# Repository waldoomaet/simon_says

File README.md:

# Inspiration
[Simon Game from Wokwi](https://wokwi.com/projects/344891334169985618)

Pretty much the same game. My version includes the board design and the game logic made with OOP (as a way to dive with this paradigm into embedded systems). Go check it out to see the simulation!

# Description
This is a personal project called Simon Says (or "Simon Dice", in Spanish).

Pretty much is an Arduino Nano with four buttons, four LEDs and a buzzer (and some displays for score), which randomly generates a pattern that the user must match. Match it, and you get a point, fail, and it is game over. Pretty simple! There is also an easier game mode, intended for smaller kids, that just generates a one-step pattern (so the game simplifies to matching the color).

# Hardware
Parts list:
* 1x Arduino Nano
* 1x SPDT switch 
* 1x Terminal block
* 1x 5v buzzer
* 2x CD4033 Decade Counter IC
* 2x common cathode 7-segment display
* 4x push buttons (preferably with color caps)
* 4x LEDs (preferably that match the caps' colors)
* 6x 1k resistors

The circuit board was made using KiCad, and there are two versions:
* A single copper side version (not tested)
* A double copper side version

Each version includes all the necessary files to fabricate the board with services such as JLCPCB.

It should be possible to also use some of the homemade methods (such as the iron method), but I never tried it.

# Hardware limitations

1. THE BOARD NEED TWO JUMPERS. I didn't notice that I used two pins of the Arduino that can't be used as digital I/O (A6 and A7), so two jumpers from A7 to A5 and from A6 to A4 are necessary.

2. Due to me using some old and obscure CD4033 Decade Counter ICs as a way to get rid of them, you can only:
    * Show numbers on the displays (and none of the hex letters that you normally could use)
    * Reset the count back to 0 or increment it. This is particularly awful since you can't set a specific number or decrement the count without first resetting the count and then increment all the way to the number that you want 

3. Due to me being too cheap to use an individual pin, of the many that the Arduino offers, for every led/button, I ended up sharing the same pin for a button and a LED, and then switch between the pin being an output or an input as needed. This ended up biting me right in the butt, as this was:

    * More annoying than it needed to be, implementing in software
    * Limiting in the sense that you can't easily, for example, play an animation and also get user input

# Software

On the software side of things, there are two important directories:
* *./src*, which have the initializing/main code
* *./lib/game_system*, which have all the game logic

The files on those directories are the main one to change in order to make any modification to the game. 

For example, to change from the normal game mode to the simpler one, you have to go tho the *main.cpp* in *./src*, and change the method called in loop:

```cpp
void loop()
{
    // This is the normal game mode. Default
    gameSystem.gameMode1();

    // Simpler version (matching colors)
    // gameSystem.gameMode2();
    
    // This is some kind of "menu" to ask every time the desired game mode
    // gameSystem.selectGameMode();
}
```

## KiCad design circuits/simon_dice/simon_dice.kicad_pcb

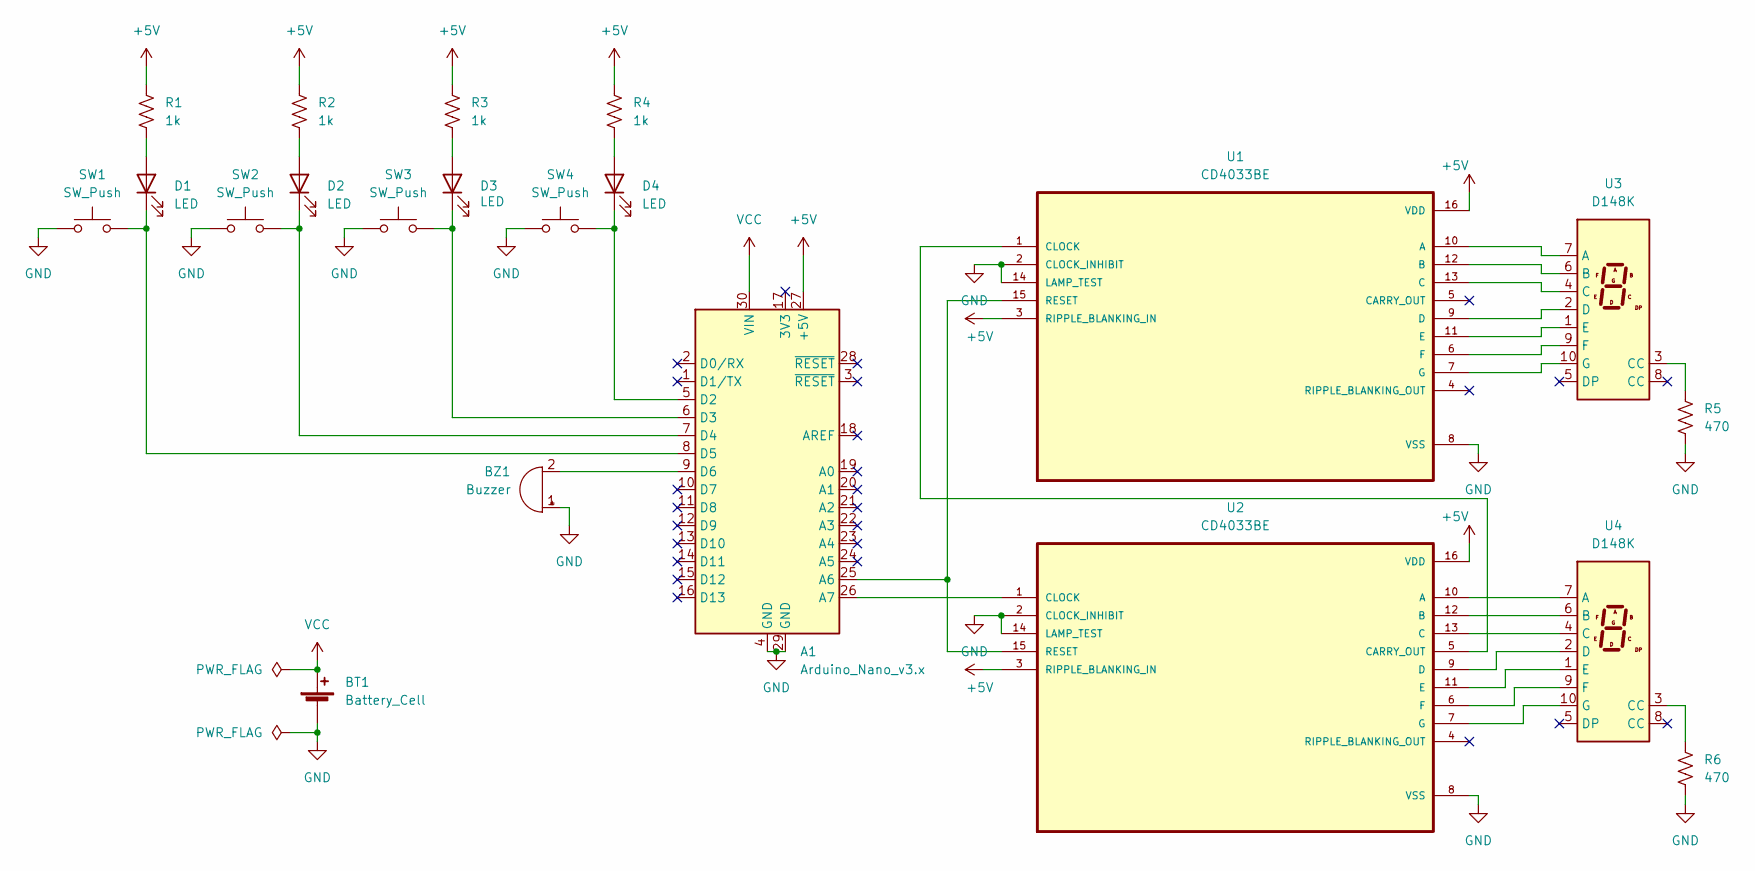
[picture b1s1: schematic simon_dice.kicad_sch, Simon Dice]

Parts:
A1: Arduino_Nano_v3.x; Arduino_Nano
BT1: Battery_Cell; PhoenixContact_MSTBA_2,5_2-G-5,08_1x02_P5.08mm_Horizontal
BZ1: Buzzer; Buzzer_12x9.5RM7.6
D1, D2, D3, D4: LED; LED_D3.0mm
R1, R2, R3, R4: 1k; R_Axial_DIN0204_L3.6mm_D1.6mm_P5.08mm_Horizontal
R5, R6: 470; R_Axial_DIN0204_L3.6mm_D1.6mm_P5.08mm_Horizontal
SW1, SW2, SW3, SW4: SW_Push; SW_PUSH-12mm
U1, U2: CD4033BE; DIP794W45P254L1969H508Q16
U3, U4: D148K; D1X8K

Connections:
+5V: A1.27 (+5V), R1.1, R2.1, R3.1, R4.1, U1.3 (RIPPLE_BLANKING_IN), U1.16 (VDD), U2.3 (RIPPLE_BLANKING_IN), U2.16 (VDD)
GND: A1.4 (GND), A1.29 (GND), BT1.2 (-), BZ1.1 (-), R5.2, R6.2, SW1.1, SW2.1, SW3.1, SW4.1, U1.2 (CLOCK_INHIBIT), U1.8 (VSS), U1.14 (LAMP_TEST), U2.2 (CLOCK_INHIBIT), U2.8 (VSS), U2.14 (LAMP_TEST)
unnamed: A1.5 (D2), D4.1 (K), SW4.2
unnamed: A1.6 (D3), D3.1 (K), SW3.2
unnamed: A1.7 (D4), D2.1 (K), SW2.2
unnamed: A1.8 (D5), D1.1 (K), SW1.2
unnamed: A1.9 (D6), BZ1.2 (+)
unnamed: A1.25 (A6), U1.15 (RESET), U2.15 (RESET)
unnamed: A1.26 (A7), U2.1 (CLOCK)
unnamed: D1.2 (A), R1.2
unnamed: D2.2 (A), R2.2
unnamed: D3.2 (A), R3.2
unnamed: D4.2 (A), R4.2
unnamed: R6.1, U4.3 (CC)
unnamed: U1.1 (CLOCK), U2.5 (CARRY_OUT)
unnamed: U1.6 (F), U3.9 (F)
unnamed: U1.7 (G), U3.10 (G)
unnamed: U1.9 (D), U3.2 (D)
unnamed: U1.10 (A), U3.7 (A)
unnamed: U1.11 (E), U3.1 (E)
unnamed: U1.12 (B), U3.6 (B)
unnamed: U1.13 (C), U3.4 (C)
unnamed: U2.6 (F), U4.9 (F)
unnamed: U2.7 (G), U4.10 (G)
unnamed: U2.9 (D), U4.2 (D)
unnamed: U2.10 (A), U4.7 (A)
unnamed: U2.11 (E), U4.1 (E)
unnamed: U2.12 (B), U4.6 (B)
unnamed: U2.13 (C), U4.4 (C)
unnamed: R5.1, U3.3 (CC)
VCC: A1.30 (VIN), BT1.1 (+)

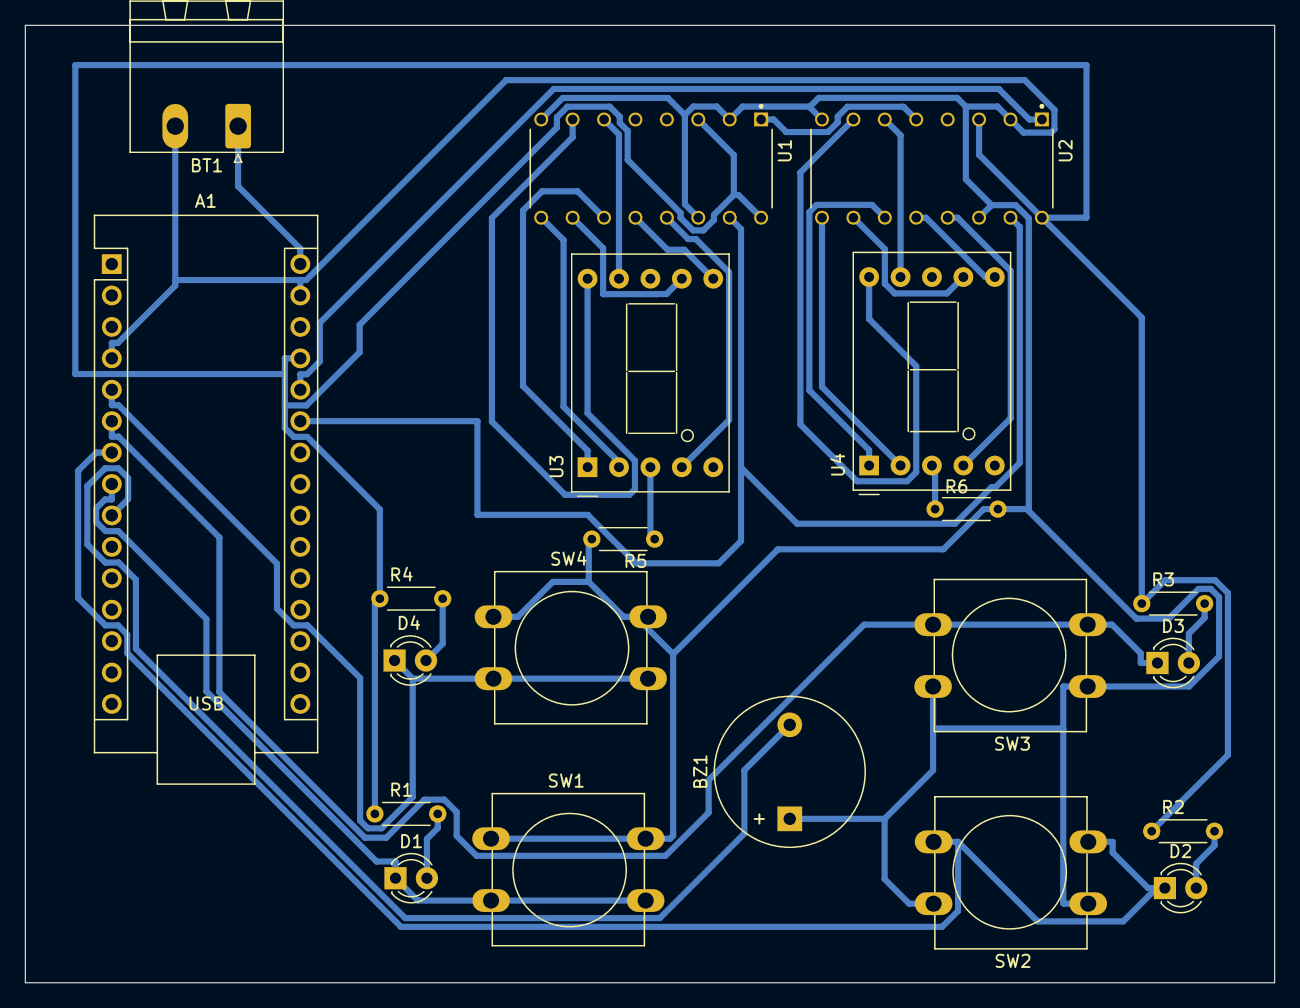
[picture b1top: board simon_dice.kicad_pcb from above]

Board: 2 copper layers, 101.0 x 77.4 mm, 21 parts (0 on the bottom side), 31 nets.

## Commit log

2023-06-11 Readme added
